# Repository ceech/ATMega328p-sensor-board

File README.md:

# ATMega328p-sensor-board
EagleCAD files

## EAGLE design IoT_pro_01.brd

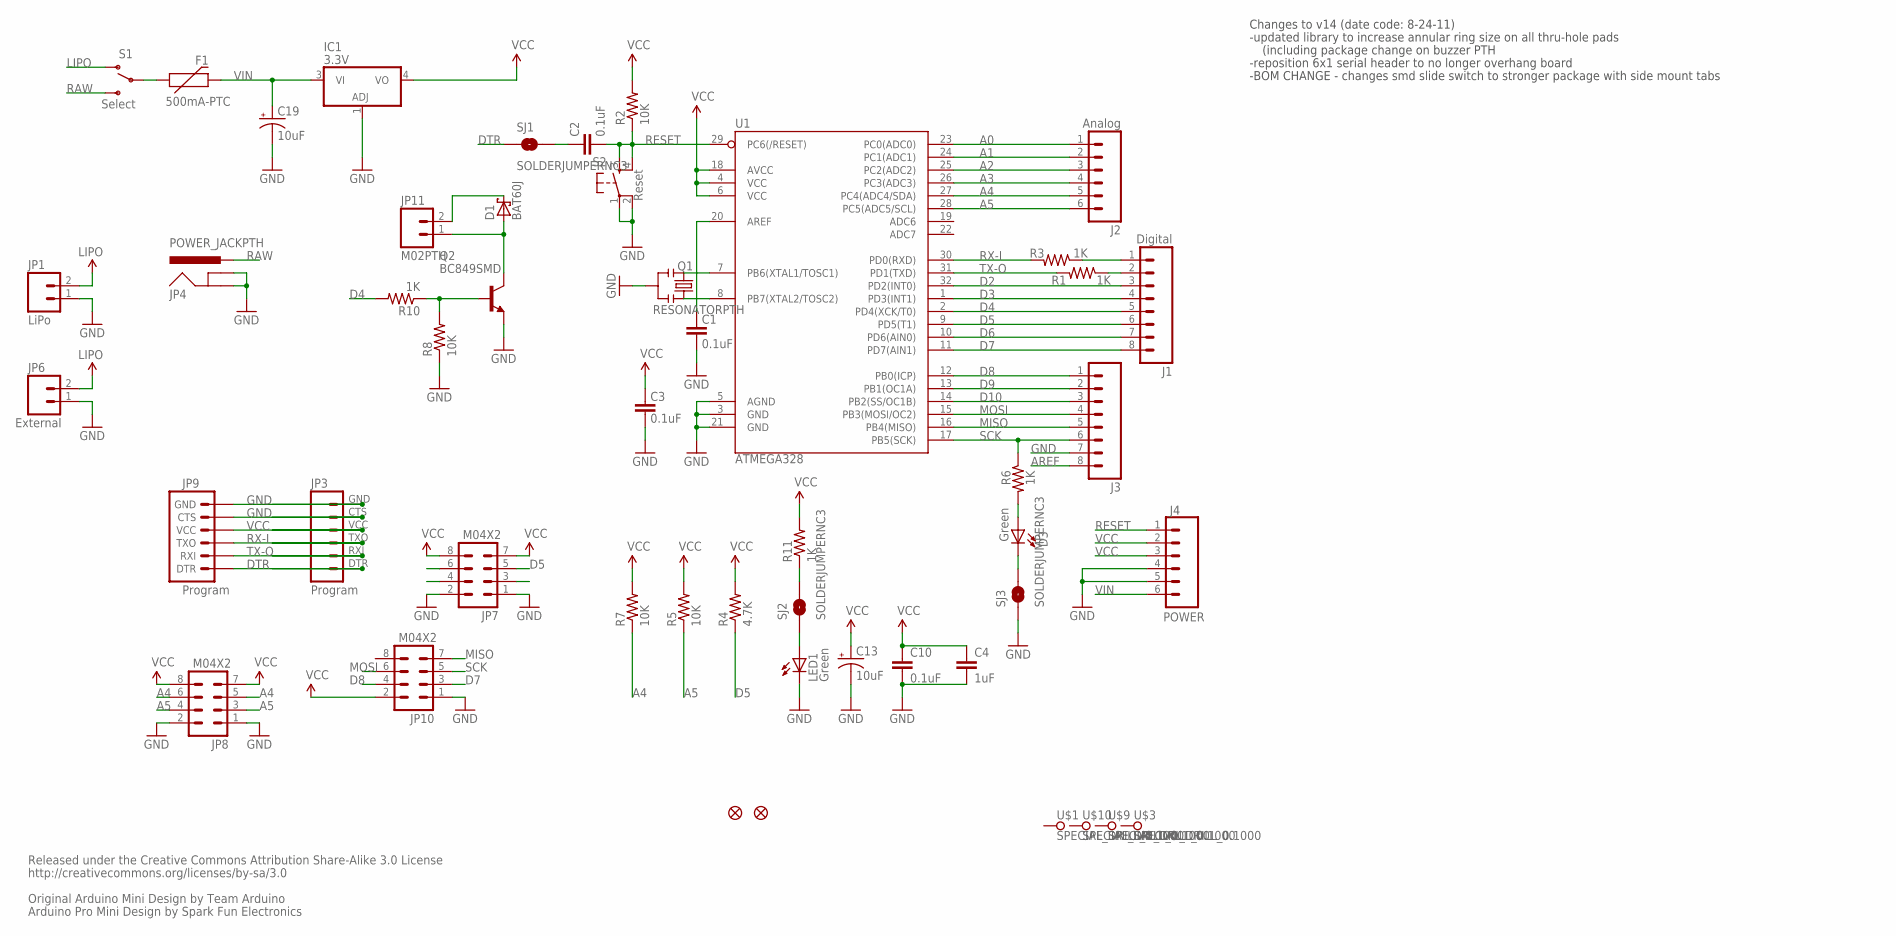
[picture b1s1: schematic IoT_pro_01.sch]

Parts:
C1, C2, C3, C10: 0.1uF; 0805
C4: 1uF; 0805
C13, C19: 10uF; EIA3216
D1: BAT60J; SOD323_ST
D3: Green; PLCC2
F1: 500mA-PTC; PTC-1206
IC1: 3.3V; SOT223
J1: Digital; 1X08
J2: Analog; 1X06
J3: M081X08; 1X08
J4: POWER; 1X06
JP1: LiPo; MOLEX-1X2
JP2, JP5: FIDUCIAL1X2.5; FIDUCIAL-1X2.5
JP3: Program; 1X06
JP4: POWER_JACKPTH; POWER_JACK_PTH
JP6: External; 1X02
JP7, JP8, JP10: M04X2; 2X4
JP9: Program; 1X06-SMD
JP11: M02PTH; 1X02
LED1: Green; PLCC2
Q1: RESONATORPTH; RESONATOR-PTH
Q2: BC849SMD; SOT23-BEC
R1, R3, R6, R10, R11: 1K; 0805
R2, R5, R7, R8: 10K; 0805
R4: 4.7K; 0805
S1: Select; SWITCH-SPDT
S2: Reset; TACTILE_SWITCH_SMD
SJ1, SJ2, SJ3: SOLDERJUMPERNC3; SJ_2S-NOTRACE
U1: ATMEGA328; TQFP32-08
U$1, U$3, U$9, U$10: SPECIAL_DRILL_0.1000; PAD_0.1000

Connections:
3.3V: JP6.2
A0: J2.1, U1.23 (PC0(ADC0))
A1: J2.2, U1.24 (PC1(ADC1))
A2: J2.3, U1.25 (PC2(ADC2))
A3: J2.4, U1.26 (PC3(ADC3))
A4: J2.5, JP8.5, JP8.6, R7.1, U1.27 (PC4(ADC4/SDA))
A5: J2.6, JP8.3, JP8.4, R5.1, U1.28 (PC5(ADC5/SCL))
AREF: C1.2, J3.8, U1.20 (AREF)
D2: J1.3, U1.32 (PD2(INT0))
D3: J1.4, U1.1 (PD3(INT1))
D4: J1.5, R10.2, U1.2 (PD4(XCK/T0))
D5: J1.6, JP7.5, R4.1, U1.9 (PD5(T1))
D6: J1.7, U1.10 (PD6(AIN0))
D7: J1.8, JP10.3, U1.11 (PD7(AIN1))
D8: J3.1, JP10.4, U1.12 (PB0(ICP))
D9: J3.2, U1.13 (PB1(OC1A))
D10: J3.3, U1.14 (PB2(SS/OC1B))
DTR: JP3.DTR (1), JP9.1 (DTR), SJ1.1
GND: C1.1, C3.1, C4.2, C10.2, C13.C (-), C19.C (-), IC1.1 (ADJ), J3.7, J4.4, J4.5, JP1.1, JP3.CTS (5), JP3.GND (6), JP4.GND, JP4.GNDBREAK, JP6.1, JP7.1, JP7.2, JP8.1, JP8.2, JP9.5 (CTS), JP9.6 (GND), JP10.1, LED1.C, Q1.2, Q2.E, R8.1, S2.1, S2.2, SJ3.1, U1.3 (GND), U1.5 (AGND), U1.21 (GND)
LIPO: JP1.2, S1.1 (O)
MISO: J3.5, JP10.7, U1.16 (PB4(MISO))
MOSI: J3.4, JP10.6, U1.15 (PB3(MOSI/OC2))
unnamed: C2.1, SJ1.2
unnamed: Q1.1, U1.8 (PB7(XTAL2/TOSC2))
unnamed: Q1.3, U1.7 (PB6(XTAL1/TOSC1))
unnamed: LED1.A, SJ2.1
unnamed: D3.A, R6.2
unnamed: R11.1, SJ2.2
unnamed: D3.C, SJ3.2
unnamed: D1.A, JP11.1, Q2.C
unnamed: D1.C, JP11.2
unnamed: Q2.B, R8.2, R10.1
unnamed: F1.1, S1.2
RAW: JP4.PWR, S1.3 (S)
RESET: C2.2, J4.1, R2.1, S2.3, S2.4, U1.29 (PC6(/RESET))
RX-I: JP3.TXO (3), JP9.3 (TXO), R3.2, U1.30 (PD0(RXD))
RX-IP: J1.2, R1.1
SCK: J3.6, JP10.5, R6.1, U1.17 (PB5(SCK))
TX-O: JP3.RXI (2), JP9.2 (RXI), R1.2, U1.31 (PD1(TXD))
TX-OP: J1.1, R3.1
VCC: C3.2, C4.1, C10.1, C13.A (+), IC1.4 (VO), J4.2, J4.3, JP3.VCC (4), JP7.7, JP7.8, JP8.7, JP8.8, JP9.4 (VCC), JP10.2, R2.2, R4.2, R5.2, R7.2, R11.2, U1.4 (VCC), U1.6 (VCC), U1.18 (AVCC)
VIN: C19.A (+), F1.2, IC1.3 (VI), J4.6

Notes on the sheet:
Released under the Creative Commons Attribution Share-Alike 3.0 License
http://creativecommons.org/licenses/by-sa/3.0
Original Arduino Mini Design by Team Arduino
Arduino Pro Mini Design by Spark Fun Electronics
Changes to v14 (date code: 8-24-11)
-updated library to increase annular ring size on all thru-hole pads
-reposition 6x1 serial header to no longer overhang board
-BOM CHANGE - changes smd slide switch to stronger package with side mount tabs
(including package change on buzzer PTH

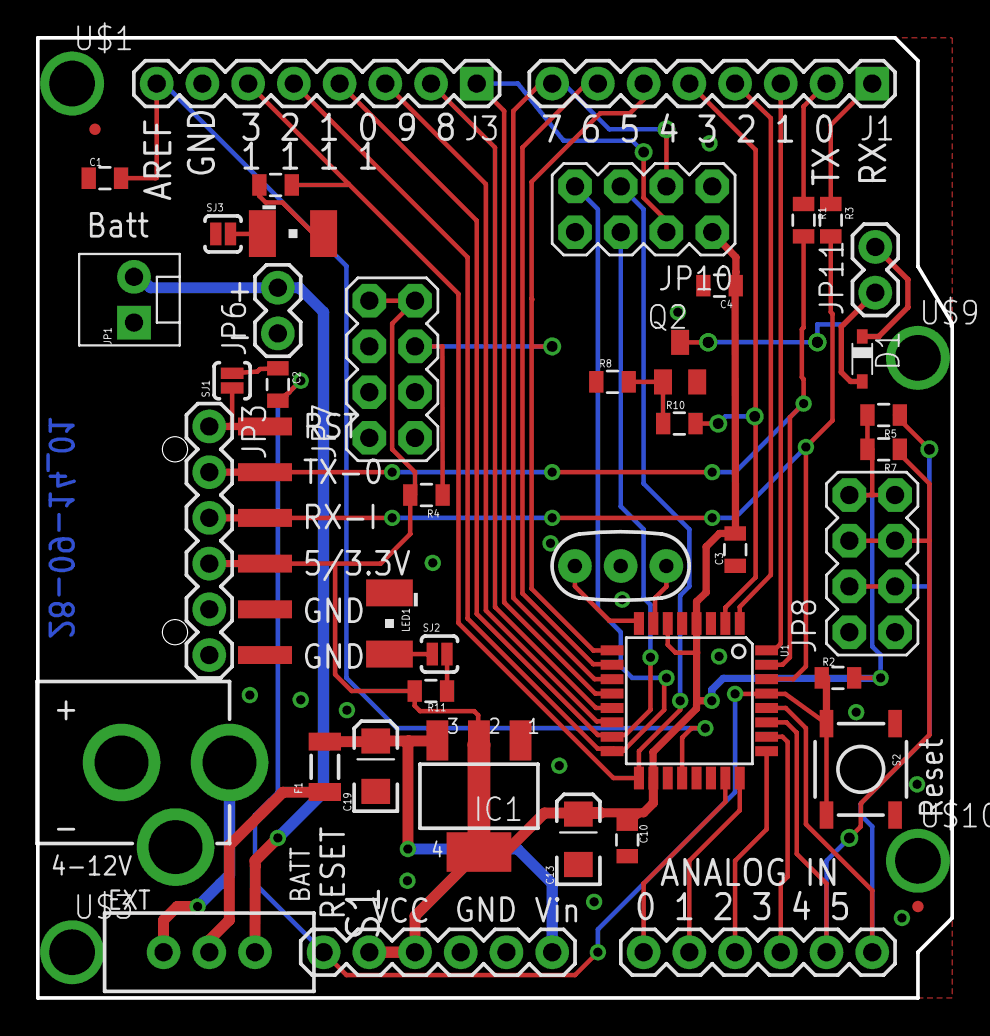
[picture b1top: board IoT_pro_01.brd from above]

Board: 2 copper layers, 50.8 x 53.3 mm, 49 parts (0 on the bottom side), 41 nets.

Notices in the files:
parts and their libraries:
SparkFun-Connectors: Licensing: Creative Commons ShareAlike 4.0 International - https://creativecommons.org/licenses/by-sa/4.0
